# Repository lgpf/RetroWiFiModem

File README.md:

# Retro WiFi modem

## An ESP8266 based RS232 \<-\> WiFi modem with Hayes AT style commands and LED indicators

## Changes Introduced

I will keep entire text from Ben readme below as it is the same.
Few changes were introduced.
1. Added sound back (a merge from original code from mecparts into Ben's code)
2. Changed the original kicad to create a new compact board that can be used with 2 differente cases.
3. A second kicad version to use MAX3232 instead MAX3237

Reason behind those changes are:
1. I was looking for something that had telnet, PPP and sound. Ben made a fork and introduced the PPP before the Sound functionality was implemented in the original project. So I just did a merge to bring it back.
2. Using original project, I changed the pcb to be suitable to custom ideas, adding headers, option for amp, external speaker, pots, different power inputs, power switch, serial header, ...
3. I am a nightmare with smd .. so I tried to do something with dip instead to make it easy for anyone, replacing all smd in the project. This one is a simple project for use in just one case (Mini Courier). It also introduced back the original problem project was facing with garbage while initializing the esp8266 (MAX3237 has enable gate, MAX3232 doesn't)

Cases I made for this project are available at Thingverse.
1. Mini Courier Modem - https://www.thingiverse.com/thing:7182022
2. Retro External Modem - https://www.thingiverse.com/thing:7182050 

Btw .. MAX3232. There is a lot of fakes out there. I tried eBay, AliExpress and some local market. All in the garbage bin.
If you want build your modem. Doesn't matter if MAX3237 or MAX3232 .. buy it from mouser or farnell.

## Original Instructions
   
This project is a small set of tweaks and updates to
[mecparts' RetroWiFiModem](https://github.com/mecparts/RetroWiFiModem) to
add some small features that I find useful and to incorporate fixes from the
firmware that go with the v2 version of the hardware.

For full documentation please see the
[v1 hardware snapshot](https://github.com/mecparts/RetroWiFiModem/releases/tag/v1.0.0)
of the original project as this README only covers the changes I have
made.

## Changes from v1 hardware snapshot

* Certain unsupported Telnet options used by a particular MUD server are
now explicitly blocked ([fixed in v2 firmware](https://github.com/mecparts/RetroWiFiModem/commit/71e6d993fff2592599ee5b3d3447f20c63cd9b56),
brought over to v1).
* Changing hardware flow control with AT&K*n* now takes effect immediately
whereas before you'd need to save your changes then restart the modem.
* AT&CS and AT&RS commands provide read/write and read-only access to the
CTS and RTS lines respectively when hardware flow control is disabled.
* AT$HOST can be used to query or change the hostname. ATI, AT&V and AT?
have also been updated to cover this new command.
* When in Telnet mode `WILL`/`WON'T`/`DO`/`DON'T` `TRANSMIT-BINARY` enable
or disable binary transmission mode for the receiver or transmitter as
appropriate. Binary transmission mode is referred to as "fake" Telnet in
the RetroWiFiModem documentation, with "real" Telnet being NVT ASCII mode.
In NVT ASCII mode `CR` is normally escaped to `CR` `NUL` unless it's a line
break (`CR` `LF`). In binary mode `CR` is left alone.
* PPP connections can be made by dialling the special number `*99#`. This
number can be changed with AT$PPP.

## Command reference

Multiple AT commands can be typed in on a single line. Spaces between
commands are allowed, but not within commands (i.e. AT S0=1 X1 Q0 is
fine; ATS 0=  1 is not). Commands that take a string as an argument
(e.g. AT$SSID=, AT$TTY=) assume that *everything* that follows is a part
of the string, so no commands are allowed after them.

Command | Details
------- | -------
+++     | Online escape code. Once your modem is connected to another device, the only command it recognises is an escape code of a one second pause followed by three typed plus signs and another one second pause, which puts the modem back into local command mode. The character used can be set with `ATS2=n`.
A/      | Repeats the last command entered. Do not type AT or press Enter.
AT      | The attention prefix that precedes all command except A/ and +++.
AT?     | Displays a help cheatsheet.
ATA     | Force the modem to answer an incoming connection when the conditions for auto answer have not been satisfied.
ATC?<br>ATC*n* | Query or change the current WiFi connection status. A result of 0 means that the modem is not connected to WiFi, 1 means the modem is connected. The command ATC0 disconnects the modem from a WiFi connection. ATC1 connects the modem to the WiFi.
ATDS*n* | Calls the host specified in speed dial slot *n* (0-9).
ATDT<i>[+=-]host[:port]</i> | Tries to establish a WiFi TCP connection to the specified host name or IP address. If no port number is given, 23 (Telnet) is assumed. You can also use ATDT to dial one of the speed dial slots in one of two ways:<br><br><ul><li>The alias in each speed dial slot is checked to see if it matches the specified hostname.</li><li>A host specified as 7 identical digits dials the slot indicated by the digit. (i.e. 2222222 would speed dial the host in slot 2).</li></ul>Preceding the host name or IP address with a +, = or - character overrides the ATNET setting for the period of the connection.<br><br><ul><li>**+** forces NET2 (fake Telnet)</li><li>**=** forces NET1 (real Telnet)</li><li>**-** forces NET0 (no Telnet)</li></ul>Once the dial attempt has begun, pressing any key before the connection is established will abort the attempt.
ATE?<br>ATE*n* | Command mode echo. Enables or disables the display of your typed commands.<br><br><ul><li>E0 Command mode echo OFF. Your typing will not appear on the screen.</li><li>E1 Command mode echo ON. Your typing will appear on the screen.</li></ul>
ATGET*http&#58;//host[/page]* | Displays the contents of a website page. **https** connections are not supported. Once the contents have been displayed, the connection will automatically terminate.
ATH | Hangs up (ends) the current connection.
ATI | Displays the current network status, including sketch build date, WiFi and call connection state, SSID name, IP address, and bytes transferred.
ATNET?<br>ATNET*n* | Query or change whether telnet protocol is enabled. A result of 0 means that telnet protocol is disabled; 1 is *Real* telnet protocol and 2 is *Fake* telnet protocol. If you are connecting to a telnet server, it may expect the modem to respond to various telnet commands, such as terminal name (set with `AT$TTY`), terminal window size (set with `AT$TTS`) or terminal speed. Telnet protocol should be enabled for these sites, or you will at best see occasional garbage characters on your screen, or at worst the connection may fail.<br><br>The difference between *real* and *fake* telnet protocol is this: with *real* telnet protocol, a carriage return (CR) character being sent from the modem to the telnet server always has a NUL character added after it. The implementation of the telnet protocol used by some BBSes doesn't properly strip out the NUL character. When connecting to such BBSes (Particles! is one), use *fake* telnet.<br><br>When using *real* telnet protocol, when the telnet server sends a CR character followed by a NUL character, only the CR character will be sent to the serial port; the NUL character will be silently stripped out. With *fake* telnet protocol, the NUL will be passed through.
ATO | Return online. Use with the escape code (+++) to toggle between command and online modes.
ATQ?<br>ATQ*n* | Enable or disable the display of result codes. The default is Q0.<br><br><ul><li>Q0 Display result codes.</li><li>Q1 Suppress result codes (quiet).</li></ul>
ATRD<br>ATRT | Displays the current UTC date and time from NIST in the format *YY-MM-DD HH:MM:SS*. A WiFi connection is required and you cannot be connected to another site.
ATS0?<br>ATS0=*n* | Display or set the number of "rings" before answering an incoming connection. Setting `S0=0` means "don't answer".
ATS2?<br>ATS2=*n* | Display or set the ASCII code used in the online escape sequence. The default value is 43 (the + plus character). Setting it to any value between 128 and 255 will disable the online escape function.
ATV?<br>ATV*n* | Display result codes in words or numbers. The default is V1.<br><br><ul><li>V0 Display result codes in numeric form.</li><li>V1 Display result codes in text form.</li></ul>
ATX?<br>ATX*n* | Control the amount of information displayed in the result codes. The default is X1 (extended codes).<br><br><ul><li>X0 Display basic codes (CONNECT, NO CARRIER)</li><li>X1 Display extended codes (CONNECT speed, NO CARRIER (connect time))</li></ul>
ATZ | Resets the modem.
AT&F | Reset the NVRAM contents and current settings to the sketch defaults. All settings, including SSID name, password and speed dial slots are affected.
AT&K?<br>AT&K*n* | Data flow control. Prevents the modem's buffers for received and transmitted from overflowing.<br><br><ul><li>&K0 Disable data flow control.</li><li>&K1 Use hardware flow control. Requires that your computer and software support Clear to Send (CTS) and Request to Send (RTS) at the RS-232 interface.</li></ul>
AT&CS?<br>AT&CS*n* | CTS status. When hardware flow control is disabled this lets you query or set the state of the CTS line.<br><br><ul><li>&CS0 de-assert CTS.</li><li>&CS1 assert CTS.</li></ul>
AT&RS? | RTS status. When hardware flow control is disabled this lets you query the state of the RTS line.
AT&R?<br>AT&R=*server pwd* | Query or change the password for incoming connections. If set, the user has 3 chances in 60 seconds to enter the correct password or the modem will end the connection.
AT&V*n* | Display current or stored settings.<br><br><ul><li>&V0 Display current settings.</li><li>&V1 Display stored settings.</li></ul>
AT&W | Save current settings to NVRAM.
AT&Zn?<br>AT&Z*n*=*host[:port],alias* | Store up to 10 numbers in NVRAM, where *n* is the position 0-9 in NVRAM, and *host[:port]* is the host string, and *alias* is the speed dial alias name. The host string may be up to 50 characters long, and the alias string may be up to 16 characters long.<br><br>Example: `AT&Z2=particlesbbs.dyndns.org:6400,particles`<br><br>This number can then be dialed in any of the following ways:<br><br><ul><li>`ATDS2`</li><li>`ATDTparticles`</li><li>`ATDT2222222`</li></ul>
AT$AE?<br>AT$AE=*startup AT cmd* | Query or change the command line to be executed when the modem starts up.
AT$AYT | Sends a Telnet "Are You There?" command if connected to a Telnet remote.
AT$BM?<br>AT$BM=*server busy msg* | Query or change a message to be returned to an incoming connection if the modem is busy (i.e. already has a connection established).
AT$MDNS?<br>AT$MDNS=*mDNS name* | Query or change the mDNS network name (defaults to "RetroWiFiModem"). When a non zero TCP port is defined, you can telnet to that port with **telnet mdnsname.local port**.
AT$HOST?<br>AT$HOST=*hostname* | Query or change the host name (defaults to ESP-*112233* where *112233* are last three bytes of the device's MAC in hexadecimal).
AT$PASS?<br>AT$PASS=*WiFi pwd* | Query or change the current WiFi password. The password is case sensitive. Clear the password by issuing the set command with no password. The maximum length of the password is 64 characters.
AT$PPP?<br>AT$PPP=*PPP number* | Query or change the number that, when dialled, establishes a PPP connection.
AT$SB?<br>AT$SB=*n* | Query or change the current baud rate. Valid values for "n" are 110, 300, 450, 600, 710, 1200, 2400, 4800, 9600, 19200, 38400, 57600, 76800 and 115200. Any other value will return an ERROR message. The default baud rate is 1200. The Retro WiFi modem does not automatically detect baud rate like a dial-up modem. The baud rate setting must match that of your terminal to operate properly. It will display garbage in your terminal otherwise.
AT$SP?<br>AT$SP=*n* | TCP server port to listen on. A value of 0 means that the TCP server is disabled, and no incoming connections are allowed.
AT$SSID?<br>AT$SSID=*ssid name* | Query or change the current SSID to the specified name. The given SSID name is case sensitive. Clear the SSID by issuing the set command with no SSID. The maximum length of the SSID name is 32 characters.
AT$SU?<br>AT$SU=*dps* | Query or change the current number of data bits ('d'), parity ('p') and stop bits ('s") of the serial UART. Valid values for 'd' are 5, 6, 7 or 8 bits. Valid values for 'p' are (N)one, (O)dd or (E)ven parity. Valid values for 's' are 1 or 2 bits. The default settings are 8N1. The UART setting must match your terminal to work properly.
AT$TTL?<br>AT$TTL=*telnet location* | Query or change the Telnet location value to be returned when the Telnet server issues a SEND-LOCATION request. The default value is "Computer Room".
AT$TTS?<br>AT$TTS=*WxH* | Query or change the window size (columns x rows) to be returned when the Telnet server issues a NAWS (Negotiate About Window Size) request. The default value is 80x24. For terminals that are smaller than 80x24, setting these values appropriately will enable paging on the help (AT?) and network status (ATI) commands.
AT$TTY?<br>AT$TTY=*terminal type* | Query or change the terminal type to be returned when the Telnet server issues a TERMINAL-TYPE request. The default value is "ansi".
AT$W?<br>AT$W=*n* | Startup wait.<br><br><ul><li>$W=0 Startup with no wait.</li><li>$W=1 Wait for the return key to be pressed at startup.</li></ul>

## References

* [mecparts' RetroWiFiModem](https://github.com/mecparts/RetroWiFiModem)
* [ssshake's vintage-computer-wifi-modem](https://github.com/ssshake/vintage-computer-wifi-modem/)

## Acknowledgements

* Thank you to mecparts for sharing their excellent work!
* The PPP implementation was heavily cribbed from ssshake's vintage-computer-wifi-modem.

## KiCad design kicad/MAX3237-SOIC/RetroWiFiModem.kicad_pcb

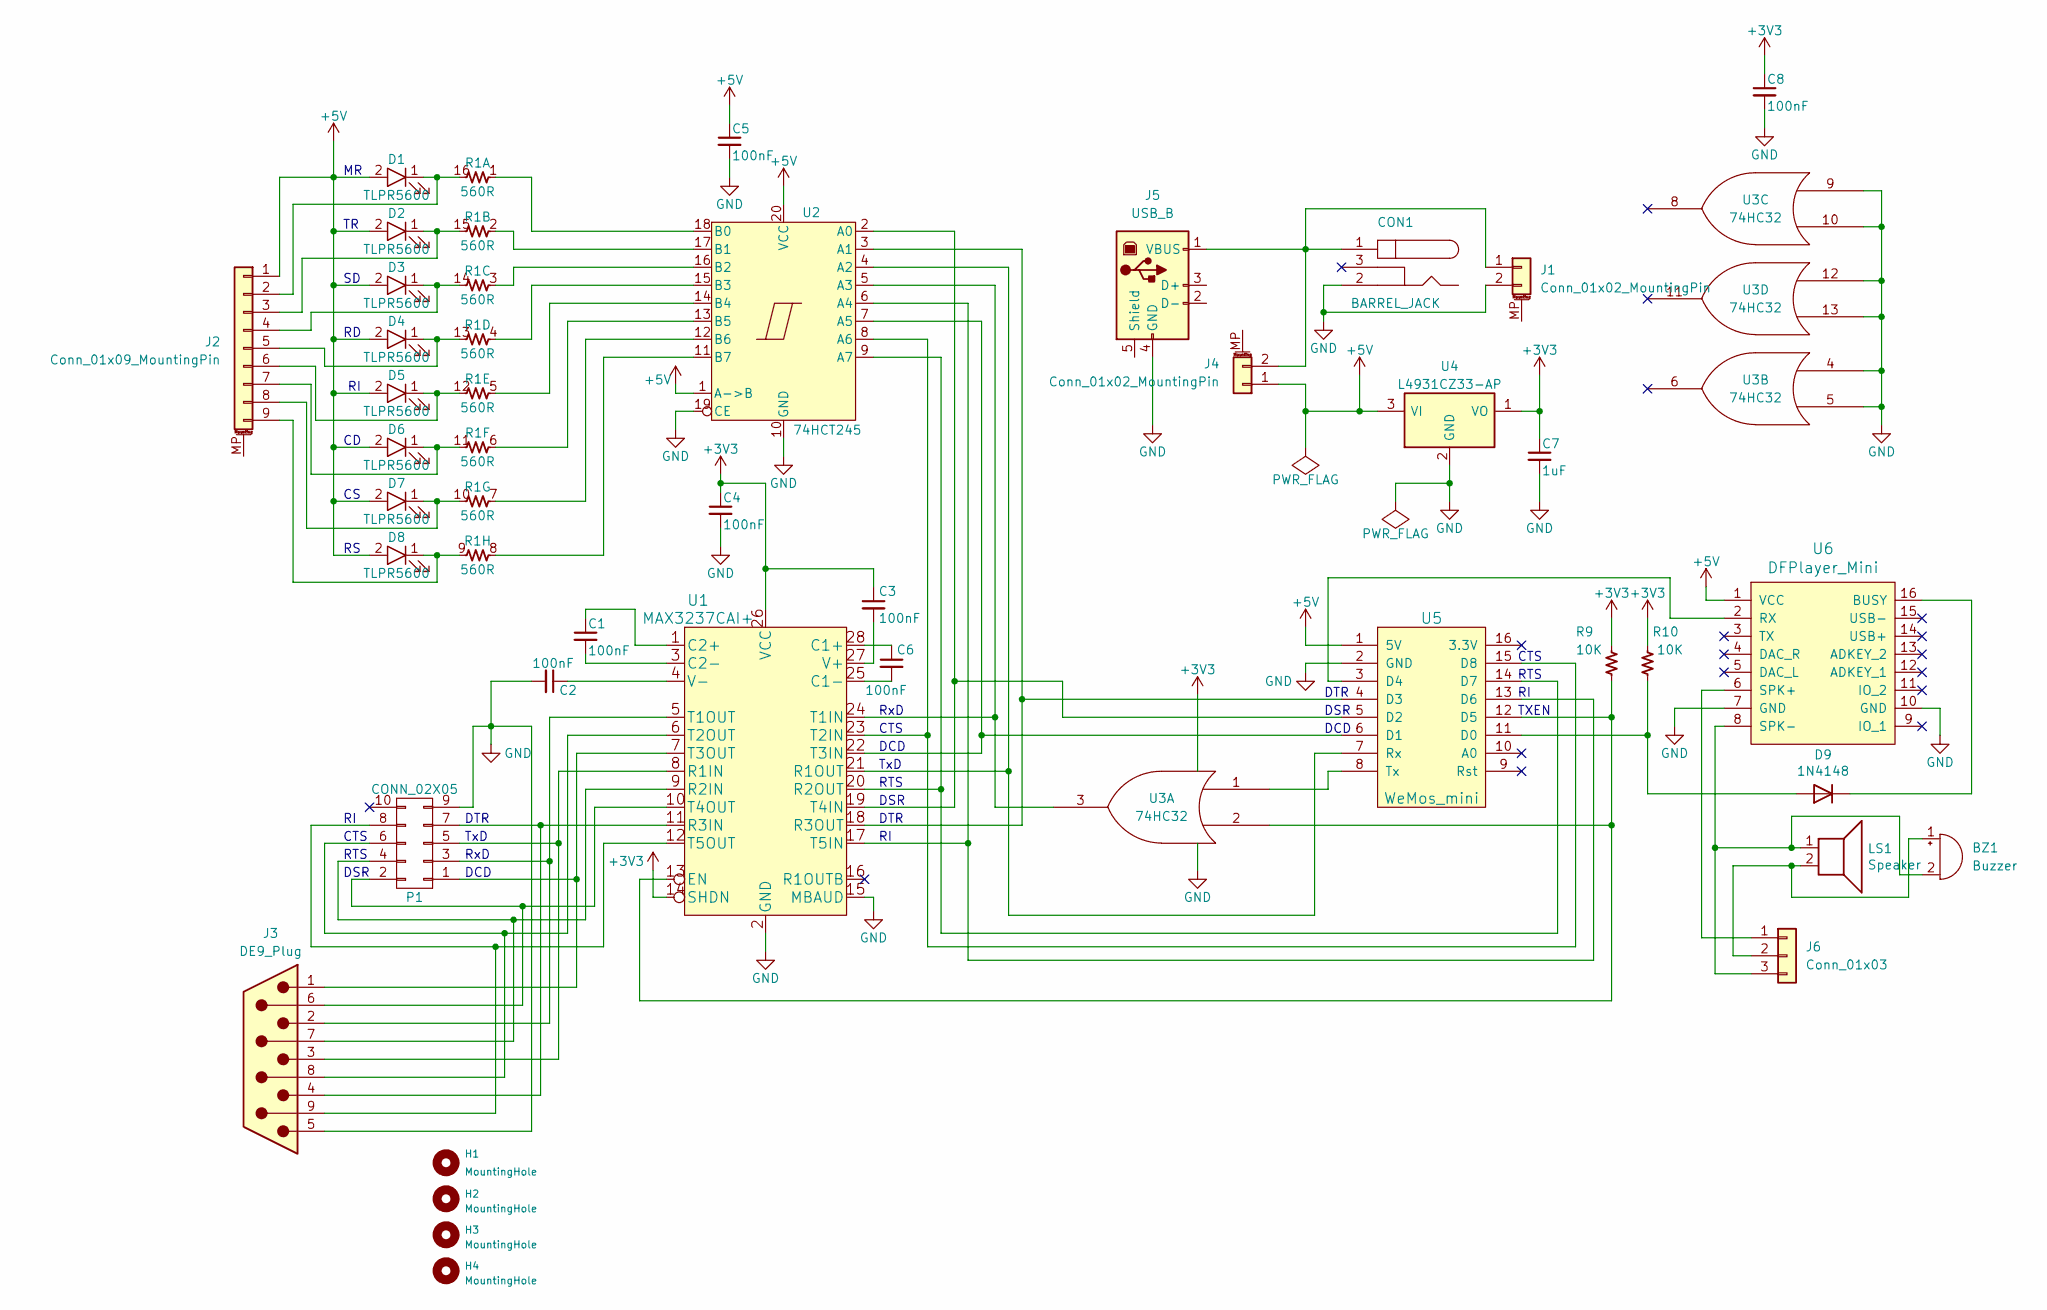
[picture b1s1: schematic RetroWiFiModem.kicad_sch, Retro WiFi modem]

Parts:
BZ1: Buzzer; Buzzer_12x9.5RM7.6
C1, C2, C3, C4, C5, C8: 100nF; C_Disc_D4.3mm_W1.9mm_P5.00mm; DigiKey PN 399-9859-1-ND
C6: 100nF; C_Disc_D4.3mm_W1.9mm_P5.00mm; DigiKey PN 399-9843-ND
C7: 1uF; C_Disc_D4.3mm_W1.9mm_P5.00mm; DigiKey PN 399-3529-ND
CON1: BARREL_JACK; BarrelJack_Horizontal; DigiKey PN 839-54-00166-ND
D1, D2, D3, D4, D5, D6, D7, D8: TLPR5600; LED-3MM; DigiKey PN TLPR5600-ND
D9: 1N4148; D_DO-35_SOD27_P7.62mm_Horizontal
H1, H2, H3, H4: MountingHole; MountingHole_3.2mm
J1, J4: Conn_01x02_MountingPin; PinHeader_1x02_P2.54mm_Vertical
J2: Conn_01x09_MountingPin; PinHeader_1x09_P2.54mm_Vertical
J3: DE9_Plug; DSUB-9_Female_Horizontal_P2.77x2.84mm_EdgePinOffset7.70mm_H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
J5: USB_B; USB_B_OST_USB-B1HSxx_Horizontal
J6: Conn_01x03; PinHeader_1x03_P2.54mm_Vertical
LS1: Speaker; PinHeader_1x02_P2.54mm_Vertical
P1: CONN_02X05; IDC_Header_Straight_10pins; DigiKey PN ED1543-ND
R1: 560R; DIP-16_W7.62mm_LongPads; DigiKey PN CF18JT560RCT-ND
R9, R10: 10K; R3; DigiKey PN CF18JT10K0CT-ND
U1: MAX3237CAI+; SOIC-28W_7.5x17.9mm_Pitch1.27mm
U2: 74HCT245; SOIC-20W_7.5x12.8mm_P1.27mm
U3: 74HC32; SOIC-14_3.9x8.7mm_P1.27mm; DigiKey PN 296-1589-5-ND
U4: L4931CZ33-AP; TO-92_Inline_Wide; DigiKey PN LP2950ACZ-3.3GOS-ND
U5: WeMos_mini; wemos-d1-mini-with-pin-header-and-connector
U6: DFPlayer_Mini; DFPlayerMini

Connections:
+3V3: C3.1, C4.1, C7.1, C8.1, R9.1, R10.1, U1.14 (SHDN), U1.26 (VCC), U3.14 (VCC), U4.1 (VO)
+5V: C5.1, D1.2 (A), D2.2 (A), D3.2 (A), D4.2 (A), D5.2 (A), D6.2 (A), D7.2 (A), D8.2 (A), J2.1, J4.1, U2.1 (A->B), U2.20 (VCC), U4.3 (VI), U5.1 (5V), U6.1 (VCC)
GND: C2.2, C4.2, C5.2, C7.2, C8.2, CON1.2, J1.2, J3.5, J5.4 (GND), P1.9, U1.2 (GND), U1.15 (MBAUD), U2.10 (GND), U2.19 (CE), U3.4, U3.5, U3.7 (GND), U3.9, U3.10, U3.12, U3.13, U4.2 (GND), U5.2 (GND), U6.7 (GND), U6.10 (GND)
unnamed: BZ1.1 (+), J6.2, LS1.2
unnamed: BZ1.2 (-), J6.3, LS1.1, U6.8 (SPK-)
unnamed: D1.1 (K), J2.2, R1.16 (R1.2)
unnamed: D2.1 (K), J2.3, R1.15 (R1.2)
unnamed: D3.1 (K), J2.4, R1.14 (R1.2)
unnamed: D4.1 (K), J2.5, R1.13 (R1.2)
unnamed: D5.1 (K), J2.6, R1.12 (R1.2)
unnamed: D6.1 (K), J2.7, R1.11 (R1.2)
unnamed: D7.1 (K), J2.8, R1.10 (R1.2)
unnamed: D8.1 (K), J2.9, R1.9 (R1.2)
unnamed: D9.2 (A), R10.2, U5.11 (D0)
unnamed: D9.1 (K), U6.16 (BUSY)
unnamed: CON1.1, J1.1, J4.2, J5.1 (VBUS)
unnamed: J6.1, U6.6 (SPK+)
unnamed: J3.1, P1.1, U1.7 (T3OUT)
unnamed: J3.6, P1.2, U1.10 (T4OUT)
unnamed: J3.2, P1.3, U1.5 (T1OUT)
unnamed: J3.7, P1.4, U1.9 (R2IN)
unnamed: J3.3, P1.5, U1.8 (R1IN)
unnamed: J3.8, P1.6, U1.6 (T2OUT)
unnamed: J3.4, P1.7, U1.11 (R3IN)
unnamed: J3.9, P1.8, U1.12 (T5OUT)
unnamed: R1.1 (R1.1), U2.18 (B0)
unnamed: R1.2 (R1.1), U2.17 (B1)
unnamed: R1.3 (R1.1), U2.16 (B2)
unnamed: R1.4 (R1.1), U2.15 (B3)
unnamed: R1.5 (R1.1), U2.14 (B4)
unnamed: R1.6 (R1.1), U2.13 (B5)
unnamed: R1.7 (R1.1), U2.12 (B6)
unnamed: R1.8 (R1.1), U2.11 (B7)
unnamed: C6.1, U1.28 (C1+)
unnamed: C6.2, U1.25 (C1-)
unnamed: C1.1, U1.1 (C2+)
unnamed: C1.2, U1.3 (C2-)
unnamed: R9.2, U1.13 (EN), U3.2, U5.12 (D5)
unnamed: U1.21 (R1OUT), U2.4 (A2), U5.7 (Rx)
unnamed: U1.20 (R2OUT), U2.9 (A7), U5.14 (D7)
unnamed: U1.18 (R3OUT), U2.3 (A1), U5.4 (D3)
unnamed: U1.24 (T1IN), U2.5 (A3), U3.3
unnamed: U1.23 (T2IN), U2.8 (A6), U5.15 (D8)
unnamed: U1.22 (T3IN), U2.7 (A5), U5.6 (D1)
unnamed: U1.19 (T4IN), U2.2 (A0), U5.5 (D2)
unnamed: U1.17 (T5IN), U2.6 (A4), U5.13 (D6)
unnamed: C3.2, U1.27 (V+)
unnamed: C2.1, U1.4 (V-)
unnamed: U5.3 (D4), U6.2 (RX)
unnamed: U3.1, U5.8 (Tx)

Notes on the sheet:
DCD
CTS
DSR
TxD
DTR
RxD
RTS
TXEN

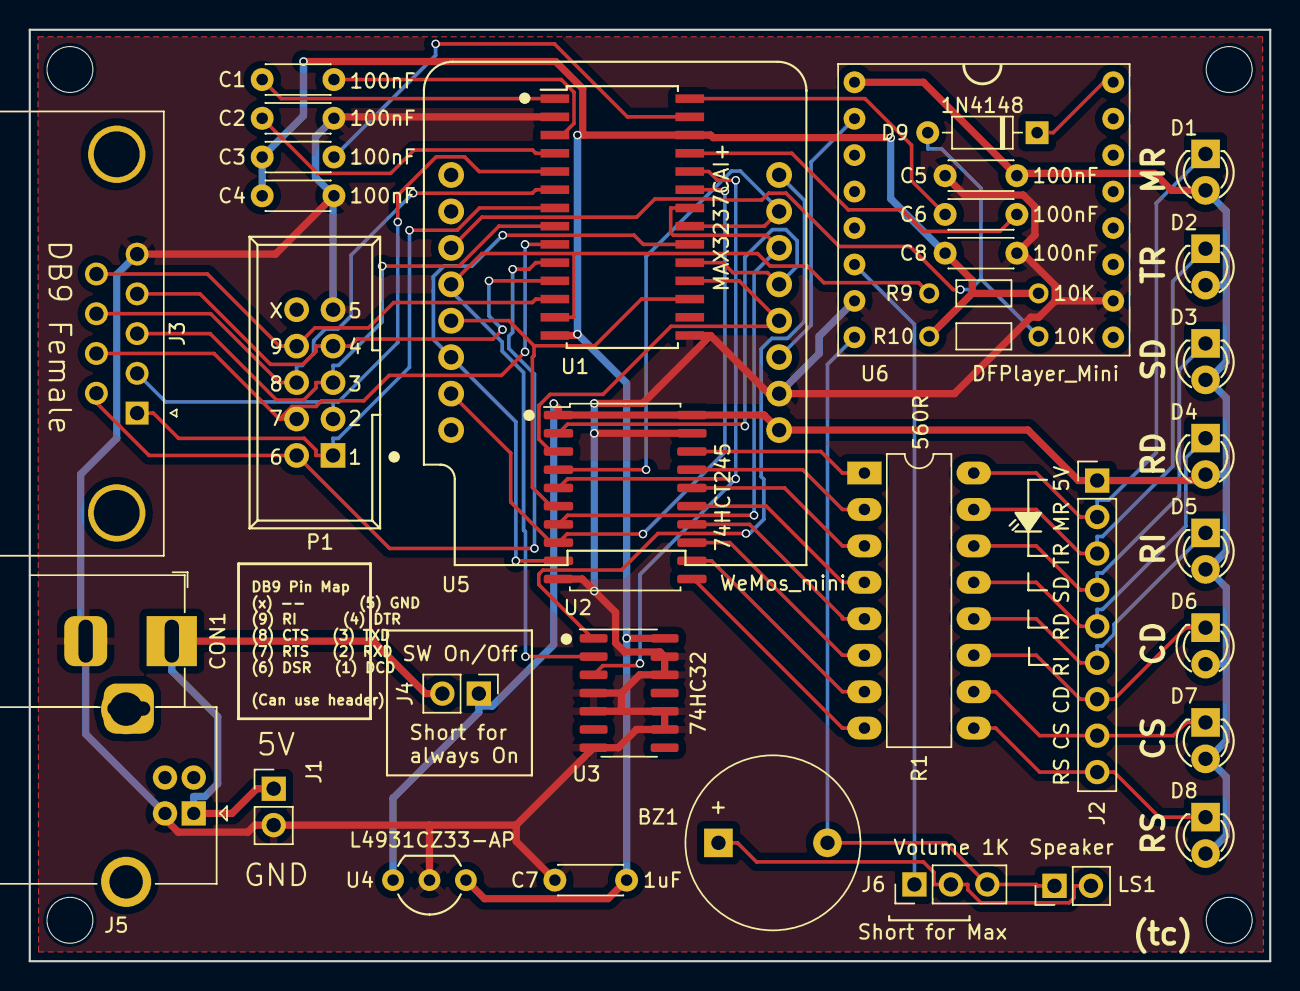
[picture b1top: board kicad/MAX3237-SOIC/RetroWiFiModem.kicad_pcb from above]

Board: 2 copper layers, 86.5 x 64.9 mm, 40 parts (0 on the bottom side), 50 nets.

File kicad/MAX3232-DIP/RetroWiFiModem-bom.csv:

Reference,Quantity, Value, DigiKey PN,BC-Robotics PN
P1,1,CONN_02X05,ED1543-ND,
U3,1,SN74HC32DR,296-1199-1-ND,
U4,1,L4931CZ33-AP,LP2950ACZ-3.3GOS-ND,
D3-D8,8,TLPR5600,TLPR5600-ND,
"C1-C2,C4-C6,C8",6,100nF,399-9859-1-ND,
C7,1,1uF,399-3529-ND,
CON1,1,BARREL_JACK,839-54-00166-ND,
R1,8,560R,CF18JT560RCT-ND,
R9-R10,2,10K,CF18JT10K0CT-ND,
U1,1,MAX3237ECDWR,296-36945-1-ND,
U2,1,74HCT245D,74HCT245DCT-ND,
C3,1,100nF,399-9859-1-ND,
U5,1,WeMos_mini,,
U6,1,DFPlayer_Mini,1738-1041-ND,
LS1,1,Speaker,,AUD-013
D9,1,1N4148,1N4148FS-ND,
,1,Hammond 1593NBK case,HM963-ND ,
,1,Hammond red panel,HM889-ND ,
,50,PCB screws,HM1442-ND,
,1,5V wall adapter,364-1251-ND ,
,1,DE-9F IDC connector,5746861-4-ND,
,2,4-40 hex standoffs,A104867-ND,
,4,8 pos machine pin socket,2057-SMC-1-08-1-GT-ND,
,1,10 pos IDC socket,1175-1443-ND ,
,1,10 cond ribbon cable,3M157815-1-ND,

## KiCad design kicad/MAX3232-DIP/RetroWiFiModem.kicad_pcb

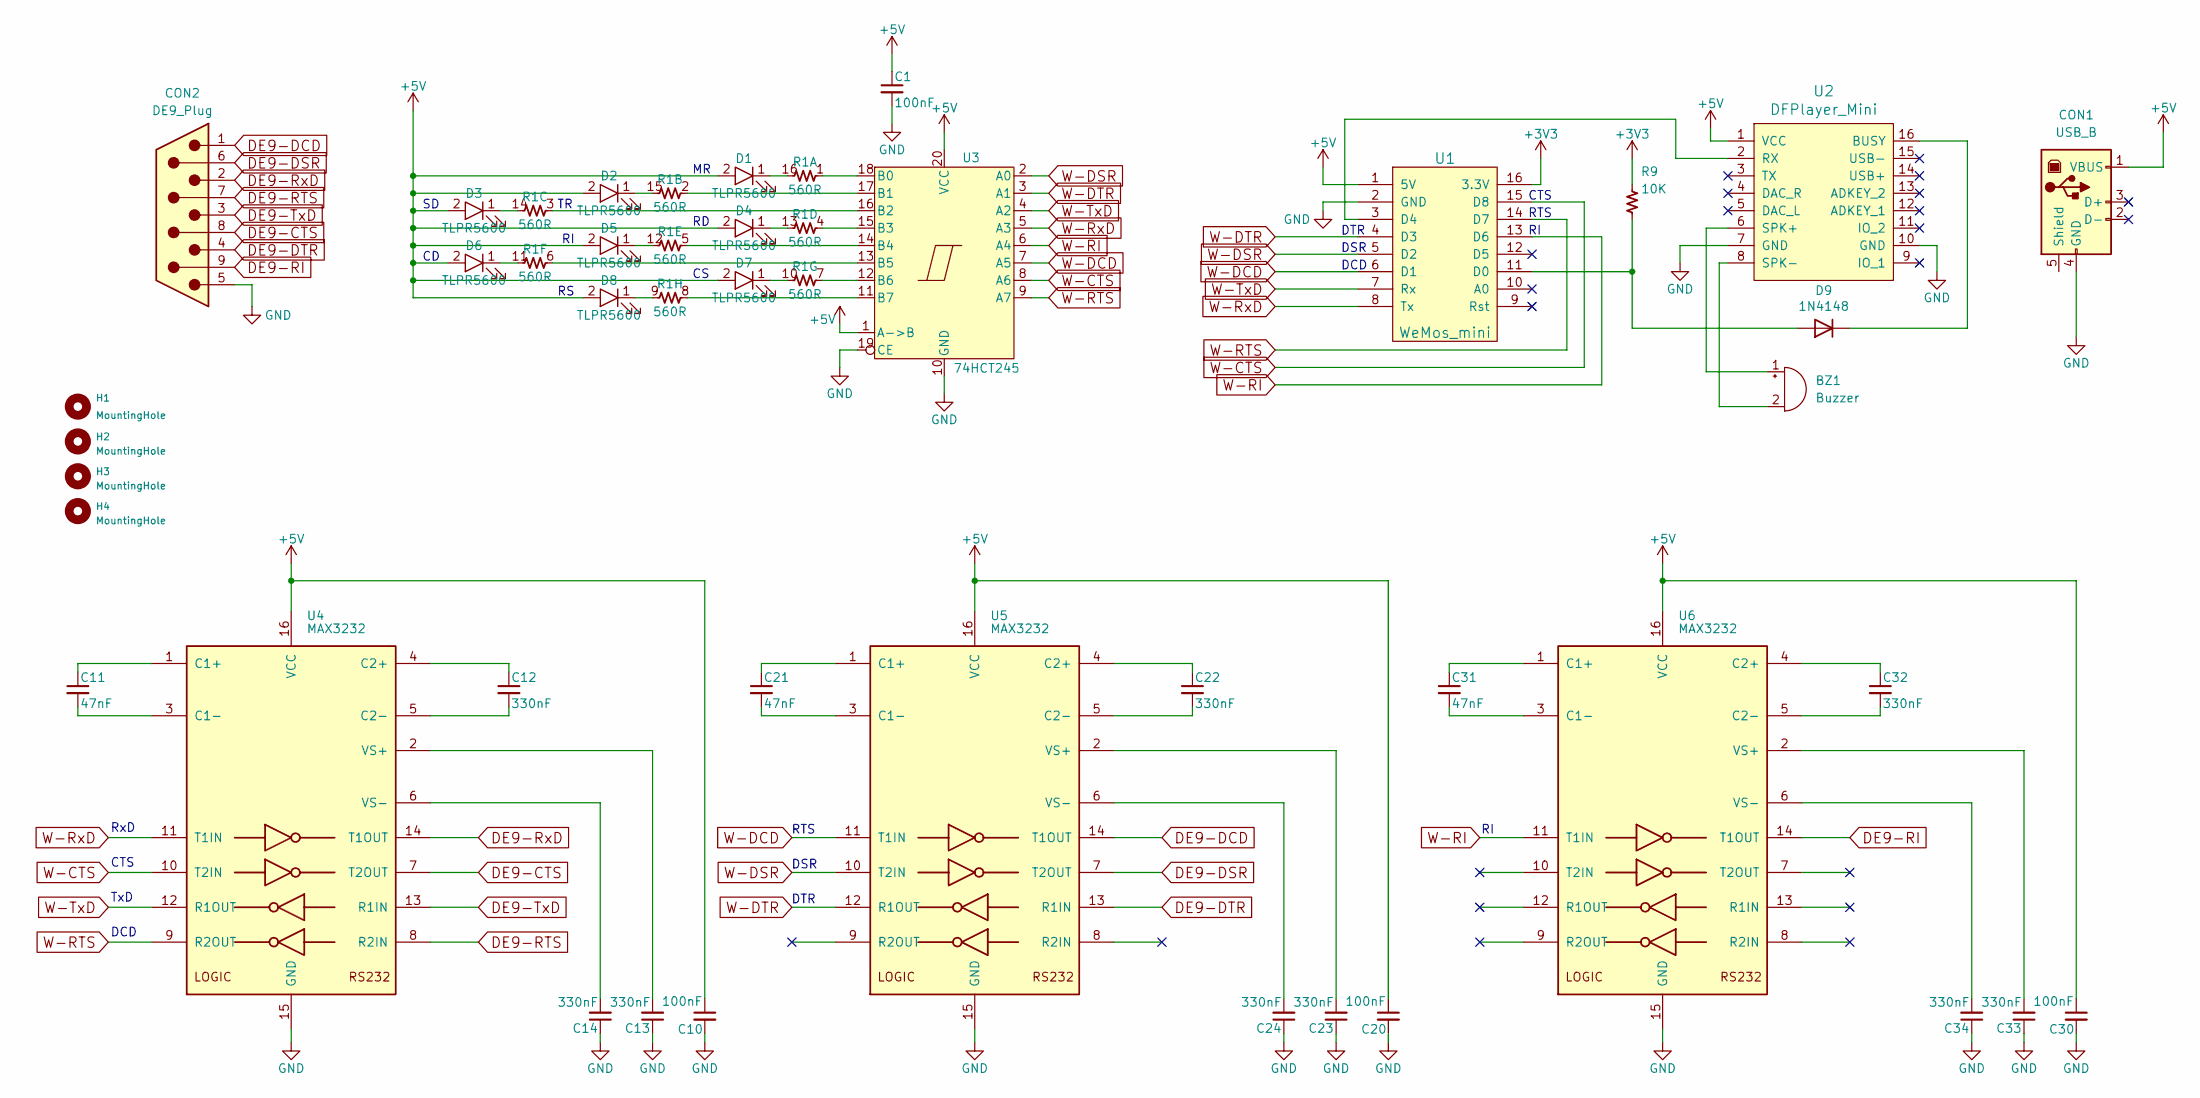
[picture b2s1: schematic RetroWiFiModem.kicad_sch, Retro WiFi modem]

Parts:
BZ1: Buzzer; Buzzer_12x9.5RM7.6
C1, C10, C20, C30: 100nF; C_Disc_D4.3mm_W1.9mm_P5.00mm; DigiKey PN 399-9859-1-ND
C11, C21, C31: 47nF; C_Disc_D4.3mm_W1.9mm_P5.00mm; DigiKey PN 399-9859-1-ND
C12, C13, C14, C22, C23, C24, C32, C33, C34: 330nF; C_Disc_D4.3mm_W1.9mm_P5.00mm; DigiKey PN 399-9859-1-ND
CON1: USB_B; USB_B_OST_USB-B1HSxx_Horizontal
CON2: DE9_Plug; DSUB-9_Female_Horizontal_P2.77x2.84mm_EdgePinOffset7.70mm_H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
D1, D2, D3, D4, D5, D6, D7, D8: TLPR5600; LED-3MM; DigiKey PN TLPR5600-ND
D9: 1N4148; D_DO-34_SOD68_P7.62mm_Horizontal
H1, H2, H3, H4: MountingHole; MountingHole_3.2mm
R1: 560R; DIP-16_W7.62mm_LongPads; DigiKey PN CF18JT560RCT-ND
R9: 10K; R_Axial_DIN0204_L3.6mm_D1.6mm_P7.62mm_Horizontal; DigiKey PN CF18JT10K0CT-ND
U1: WeMos_mini; wemos-d1-mini-with-pin-header-and-connector
U2: DFPlayer_Mini; DFPlayerMini
U3: 74HCT245; DIP-20_W7.62mm_LongPads
U4, U5, U6: MAX3232; DIP-16_W7.62mm_LongPads

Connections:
+3V3: R9.1, U1.16 (3.3V)
+5V: C1.1, C10.1, C20.1, C30.1, CON1.1 (VBUS), D1.2 (A), D2.2 (A), D3.2 (A), D4.2 (A), D5.2 (A), D6.2 (A), D7.2 (A), D8.2 (A), U1.1 (5V), U2.1 (VCC), U3.1 (A->B), U3.20 (VCC), U4.16 (VCC), U5.16 (VCC), U6.16 (VCC)
DE9-CTS: CON2.8, U4.7 (T2OUT)
DE9-DCD: CON2.1, U5.14 (T1OUT)
DE9-DSR: CON2.6, U5.7 (T2OUT)
DE9-DTR: CON2.4, U5.13 (R1IN)
DE9-RI: CON2.9, U6.14 (T1OUT)
DE9-RTS: CON2.7, U4.8 (R2IN)
DE9-RxD: CON2.2, U4.14 (T1OUT)
DE9-TxD: CON2.3, U4.13 (R1IN)
GND: C1.2, C10.2, C13.1, C14.1, C20.2, C23.1, C24.1, C30.2, C33.1, C34.1, CON1.4 (GND), CON2.5, U1.2 (GND), U2.7 (GND), U2.10 (GND), U3.10 (GND), U3.19 (CE), U4.15 (GND), U5.15 (GND), U6.15 (GND)
unnamed: BZ1.1 (+), U2.6 (SPK+)
unnamed: BZ1.2 (-), U2.8 (SPK-)
unnamed: D1.1 (K), R1.16 (R1.2)
unnamed: D2.1 (K), R1.15 (R1.2)
unnamed: D3.1 (K), R1.14 (R1.2)
unnamed: D4.1 (K), R1.13 (R1.2)
unnamed: D5.1 (K), R1.12 (R1.2)
unnamed: D6.1 (K), R1.11 (R1.2)
unnamed: D7.1 (K), R1.10 (R1.2)
unnamed: D8.1 (K), R1.9 (R1.2)
unnamed: D9.2 (A), R9.2, U1.11 (D0)
unnamed: D9.1 (K), U2.16 (BUSY)
unnamed: R1.1 (R1.1), U3.18 (B0)
unnamed: R1.2 (R1.1), U3.17 (B1)
unnamed: R1.3 (R1.1), U3.16 (B2)
unnamed: R1.4 (R1.1), U3.15 (B3)
unnamed: R1.5 (R1.1), U3.14 (B4)
unnamed: R1.6 (R1.1), U3.13 (B5)
unnamed: R1.7 (R1.1), U3.12 (B6)
unnamed: R1.8 (R1.1), U3.11 (B7)
unnamed: U1.3 (D4), U2.2 (RX)
unnamed: C11.1, U4.1 (C1+)
unnamed: C11.2, U4.3 (C1-)
unnamed: C12.1, U4.4 (C2+)
unnamed: C12.2, U4.5 (C2-)
unnamed: C13.2, U4.2 (VS+)
unnamed: C14.2, U4.6 (VS-)
unnamed: C21.1, U5.1 (C1+)
unnamed: C21.2, U5.3 (C1-)
unnamed: C22.1, U5.4 (C2+)
unnamed: C22.2, U5.5 (C2-)
unnamed: C23.2, U5.2 (VS+)
unnamed: C24.2, U5.6 (VS-)
unnamed: C31.1, U6.1 (C1+)
unnamed: C31.2, U6.3 (C1-)
unnamed: C32.1, U6.4 (C2+)
unnamed: C32.2, U6.5 (C2-)
unnamed: C33.2, U6.2 (VS+)
unnamed: C34.2, U6.6 (VS-)
W-CTS: U1.15 (D8), U3.8 (A6), U4.10 (T2IN)
W-DCD: U1.6 (D1), U3.7 (A5), U5.11 (T1IN)
W-DSR: U1.5 (D2), U3.2 (A0), U5.10 (T2IN)
W-DTR: U1.4 (D3), U3.3 (A1), U5.12 (R1OUT)
W-RI: U1.13 (D6), U3.6 (A4), U6.11 (T1IN)
W-RTS: U1.14 (D7), U3.9 (A7), U4.9 (R2OUT)
W-RxD: U1.8 (Tx), U3.5 (A3), U4.11 (T1IN)
W-TxD: U1.7 (Rx), U3.4 (A2), U4.12 (R1OUT)

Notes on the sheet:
DCD
CTS
DSR
TxD
DTR
RxD
RTS

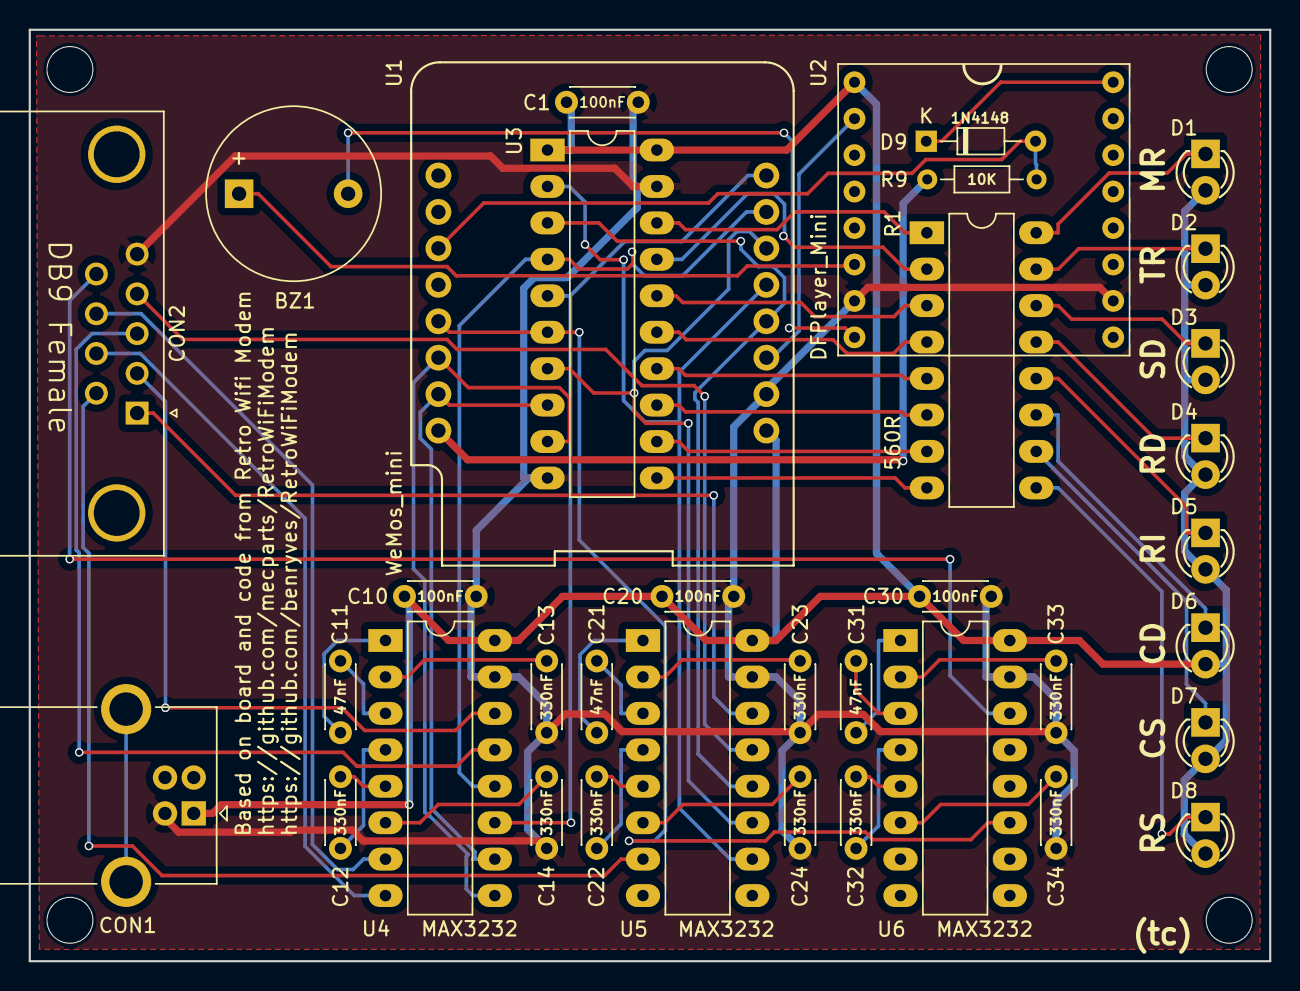
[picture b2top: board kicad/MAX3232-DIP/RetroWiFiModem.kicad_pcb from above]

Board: 2 copper layers, 86.5 x 64.9 mm, 40 parts (0 on the bottom side), 58 nets.
